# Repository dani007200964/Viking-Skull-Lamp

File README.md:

# Viking Skull Lamp 

## Introduction

I ​made this project for my brother. He loves Halloween and asked me to create a Viking-style lamp that has a glowing skull.
This is what comes out of this idea. I roughly had five months to test the device before publishing it. I can happily say
that in this period nothing went wrong with it. It just worked like a charm. Also, I have worked a lot on the documentation,
meanwhile. Here you can see what can this thing do.

## Features:
* 30 addressable LED to make it shine :rotating_light:
* Microphone for :studio_microphone:
  * Music reactive lighting :musical_note:
  * @ref clap_pattern "Clap switch" :clap:
* Foldable controls
* Interactive menu with a graphical display :joystick:
* Saving and loading the configuration parameters :floppy_disk:
* Light modes:
  * Rainbow :rainbow:
  * Candle :candle:
  * Pulse :loud_sound:
  * Komodo 3000 :sunny:
  * Color :art:
* Humidifier for spooky smoke effect :ghost:
* Magic runes on the front. They are glow-in-the-dark :star:

## Documentation

The full documentation with detailed assembly instructions can be found [here](https://dani007200964.github.io/Viking-Skull-Lamp/html/index.html).

## Donation

If you like my work, and if it was useful for you, please consider buying me a coffee or tipping. :coffee: :coffee: :coffee:

<a href='https://ko-fi.com/danielhajnal' target='_blank'>

## Contributing

Pull requests are welcome. For major changes, please open an issue first to discuss what you would like to change.

## Used Resources:

* [FastLED](https://github.com/FastLED/FastLED)
* [PlatformIO](https://platformio.org/)
* [Visual Studio Code](https://code.visualstudio.com/)
* [Atom](https://atom.io/)
* [Doxygen](https://doxygen.nl/manual/tables.html)
* [Doxygen Awesome Theme](https://github.com/jothepro/doxygen-awesome-css)
* [Graphviz](https://graphviz.org/)
* [FreeCAD](https://www.freecadweb.org/)
* [Blender](https://www.blender.org/)
* [Prusa Slicer](https://github.com/prusa3d/PrusaSlicer/releases)
* [Gimp](https://www.gimp.org/)
* [KiCad](https://www.kicad.org/)
* [Interactive HTML BOM](https://github.com/openscopeproject/InteractiveHtmlBom)
* [Inkscape](https://inkscape.org/)
* [OpenShot](https://www.openshot.org/)
* [model-viewer](https://modelviewer.dev/)

## License & Copyright

© Daniel Hajnal

:email: hajnal.daniel96@gmail.com

Software is licensed under the __MIT__ License, and the hardware and the mechanical parts are licensed under the __Creative Commons__ [BY-NC-SA](https://creativecommons.org/licenses/by-nc-sa/4.0/) license.

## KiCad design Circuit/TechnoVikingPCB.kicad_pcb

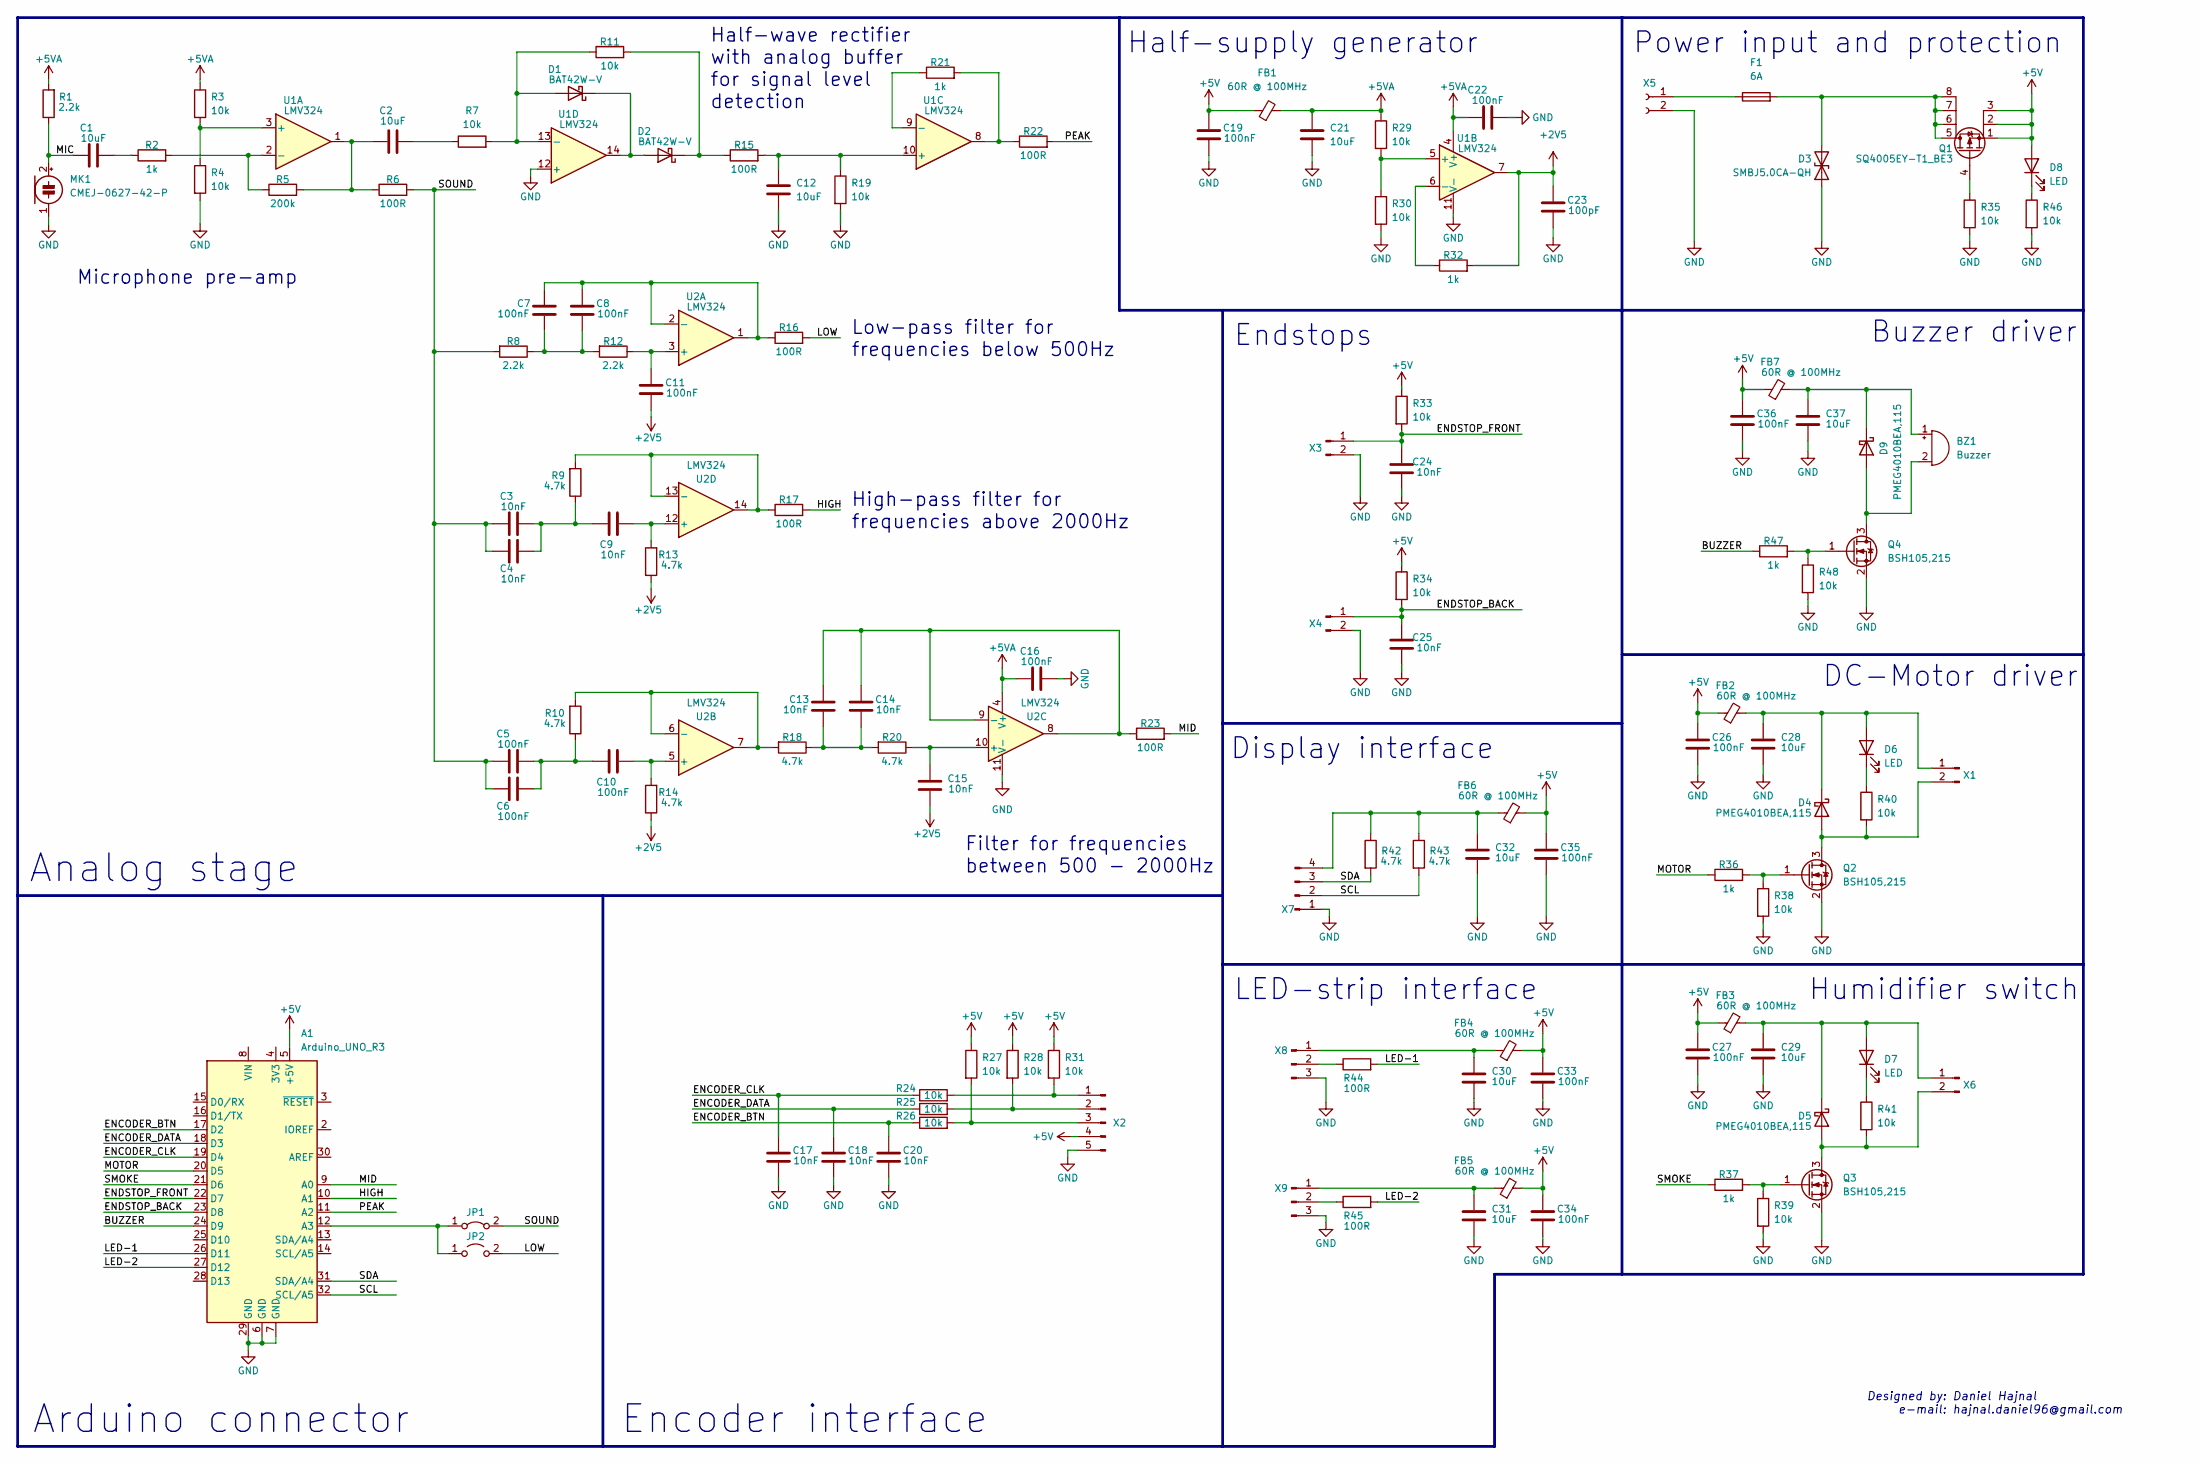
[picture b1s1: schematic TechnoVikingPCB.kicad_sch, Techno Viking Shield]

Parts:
A1: Arduino_UNO_R3; Arduino_R3_Extended; MPN 61304011121
BZ1: Buzzer; MagneticBuzzer_PUI_AT-0927-TT-6-R; MPN AT-0927-TT-6-R
C1, C2, C12, C21, C28, C29, C30, C31, C32, C37: 10uF; R_0805_2012Metric_Pad1.20x1.40mm_HandSolder; MPN GRM21BR61C106KE15K
C3, C4, C9, C13, C14, C15, C17, C18, C20, C24, C25: 10nF; R_0603_1608Metric_Pad0.98x0.95mm_HandSolder; MPN CC0603KRX7R7BB103
C5, C6, C7, C8, C10, C11, C16, C19, C22, C26, C27, C33, C34, C35, C36: 100nF; R_0603_1608Metric_Pad0.98x0.95mm_HandSolder; MPN CC0603JRX7R7BB104
C23: 100pF; R_0603_1608Metric_Pad0.98x0.95mm_HandSolder; MPN CC0603KRX7R7BB101
D1, D2: BAT42W-V; D_SOD-123; MPN BAT42W-G3-08
D3: SMBJ5.0CA-QH; D_SMB_Handsoldering; MPN SMBJ5.0CA-QH
D4, D5, D9: PMEG4010BEA,115; D_SOD-323_HandSoldering; MPN PMEG4010BEA,115
D6, D7: LED; LED_0603_1608Metric_Pad1.05x0.95mm_HandSolder; MPN APT1608SYC/J3-AMT
D8: LED; LED_0603_1608Metric_Pad1.05x0.95mm_HandSolder; MPN APT1608ZGC-AMT
F1: 6A; Fuse_1206_3216Metric_Pad1.42x1.75mm_HandSolder; MPN 0685P6000-01
FB1, FB2, FB3, FB4, FB5, FB6, FB7: 60R @ 100MHz; L_0603_1608Metric_Pad1.05x0.95mm_HandSolder; MPN BLM18PG600SZ1D
JP1: Jumper_2_Bridged; SolderJumper-2_P1.3mm_Bridged_Pad1.0x1.5mm
JP2: Jumper_2_Open; SolderJumper-2_P1.3mm_Open_Pad1.0x1.5mm
MK1: CMEJ-0627-42-P; Mic 6mm; MPN CMEJ-0627-42-P
Q1: SQ4005EY-T1_BE3; SO-8_3.9x4.9mm_P1.27mm; MPN SQ4005EY-T1_BE3
Q2, Q3, Q4: BSH105,215; SOT-23; MPN BSH105,215
R1, R8, R12: 2.2k; R_0603_1608Metric_Pad0.98x0.95mm_HandSolder; MPN CRCW06032K20FKEAC
R2, R21, R32, R36, R37, R47: 1k; R_0603_1608Metric_Pad0.98x0.95mm_HandSolder; MPN CRCW06031K00JNEC
R3, R4, R7, R11, R19, R24, R25, R26, R27, R28, R29, R30, R31, R33, R34, R35, R38, R39, R40, R41, R46, R48: 10k; R_0603_1608Metric_Pad0.98x0.95mm_HandSolder; MPN RCG060310K0FKEA
R5: 200k; R_0603_1608Metric_Pad0.98x0.95mm_HandSolder; MPN CRCW0603200KFKEAC
R6, R15, R16, R17, R22, R23, R44, R45: 100R; R_0603_1608Metric_Pad0.98x0.95mm_HandSolder; MPN CRCW0603100RJNEAC
R9, R10, R13, R14, R18, R20, R42, R43: 4.7k; R_0603_1608Metric_Pad0.98x0.95mm_HandSolder; MPN CRCW06034K70JNEC
U1, U2: LMV324; SOIC-14_3.9x8.7mm_P1.27mm; MPN LMV324IDR
X1, X3, X4, X6: Conn_01x02_Male; JST_PH_S2B-PH-K_1x02_P2.00mm_Horizontal; MPN S2B-PH-K-S (LF)(SN)
X2: Conn_01x05_Male; JST_PH_S5B-PH-K_1x05_P2.00mm_Horizontal; MPN S5B-PH-K-S (LF)(SN)
X5: Conn_01x02_Female; TerminalBlock_4Ucon_1x02_P3.50mm_Horizontal; MPN 39357-0002
X7: Conn_01x04_Male; JST_PH_S4B-PH-K_1x04_P2.00mm_Horizontal; MPN S4B-PH-K-S (LF)(SN)
X8, X9: Conn_01x03_Male; JST_PH_B3B-PH-K_1x03_P2.00mm_Vertical; MPN B3B-PH-K-S(LF)(SN)

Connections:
+2V5: C11.1, C15.1, C23.1, R13.1, R14.1, R32.2, U1.7
+5V: A1.5 (+5V), C19.2, C26.2, C27.2, C33.2, C34.2, C35.2, C36.2, D8.2 (A), FB1.1, FB2.1, FB3.1, FB4.2, FB5.2, FB6.2, FB7.1, Q1.1 (S), Q1.2 (S), Q1.3 (S), R27.1, R28.1, R31.1, R33.1, R34.1, X2.4
+5VA: C16.1, C21.2, C22.1, FB1.2, R1.2, R3.1, R29.1, U1.4 (V+), U2.4 (V+)
/BUZZER: A1.24 (D9), R47.1
/ENCODER_BTN: A1.17 (D2), C20.1, R26.1
/ENCODER_CLK: A1.19 (D4), C17.1, R24.1
/ENCODER_DATA: A1.18 (D3), C18.1, R25.1
/ENDSTOP_BACK: A1.23 (D8), C25.1, R34.2, X4.1
/ENDSTOP_FRONT: A1.22 (D7), C24.1, R33.2, X3.1
/HIGH: A1.10 (A1), R17.2
/LED-1: A1.26 (D11), R44.2
/LED-2: A1.27 (D12), R45.2
/LOW: JP2.2 (B), R16.2
/MIC: C1.1, MK1.2 (+), R1.1
/MID: A1.9 (A0), R23.2
/MOTOR: A1.20 (D5), R36.1
/PEAK: A1.11 (A2), R22.2
/SCL: A1.32 (SCL/A5), R43.2, X7.2
/SDA: A1.31 (SDA/A4), R42.2, X7.3
/SMOKE: A1.21 (D6), R37.1
/SOUND: C3.2, C4.2, C5.2, C6.2, JP1.2 (B), R6.2, R8.2
GND: A1.6 (GND), A1.7 (GND), A1.29 (GND), C12.1, C16.2, C17.2, C18.2, C19.1, C20.2, C21.1, C22.2, C23.2, C24.2, C25.2, C26.1, C27.1, C28.1, C29.1, C30.1, C31.1, C32.1, C33.1, C34.1, C35.1, C36.1, C37.1, D3.1 (A1), MK1.1 (-), Q2.2 (S), Q3.2 (S), Q4.2 (S), R4.2, R19.2, R30.2, R35.2, R38.2, R39.2, R46.2, R48.2, U1.11 (V-), U1.12 (+), U2.11 (V-), X2.5, X3.2, X4.2, X5.2, X7.1, X8.3, X9.3
unnamed: A1.12 (A3), JP1.1 (A), JP2.1 (A)
unnamed: BZ1.1 (-), C37.2, D9.1 (K), FB7.2
unnamed: BZ1.2 (+), D9.2 (A), Q4.3 (D)
unnamed: C1.2, R2.1
unnamed: C2.1, R5.2, R6.1, U1.1
unnamed: C2.2, R7.1
unnamed: C3.1, C4.1, C9.2, R9.1
unnamed: C7.1, C8.1, R8.1, R12.2
unnamed: C7.2, C8.2, R16.1, U2.1, U2.2 (-)
unnamed: C9.1, R13.2, U2.12 (+)
unnamed: C10.1, R14.2, U2.5 (+)
unnamed: C5.1, C6.1, C10.2, R10.1
unnamed: C11.2, R12.1, U2.3 (+)
unnamed: C12.2, R15.2, R19.1, U1.10 (+)
unnamed: C13.1, C14.1, R18.1, R20.2
unnamed: C13.2, C14.2, R23.1, U2.8, U2.9 (-)
unnamed: C15.2, R20.1, U2.10 (+)
unnamed: C28.2, D4.1 (K), D6.2 (A), FB2.2, X1.1
unnamed: C29.2, D5.1 (K), D7.2 (A), FB3.2, X6.1
unnamed: C30.2, FB4.1, X8.1
unnamed: C31.2, FB5.1, X9.1
unnamed: C32.2, FB6.1, R42.1, R43.1, X7.4
unnamed: D1.1 (K), D2.2 (A), U1.14
unnamed: D1.2 (A), R7.2, R11.1, U1.13 (-)
unnamed: D2.1 (K), R11.2, R15.1
unnamed: D3.2 (A2), F1.2, Q1.5 (D), Q1.6 (D), Q1.7 (D), Q1.8 (D)
unnamed: D4.2 (A), Q2.3 (D), R40.2, X1.2
unnamed: D5.2 (A), Q3.3 (D), R41.2, X6.2
unnamed: D6.1 (K), R40.1
unnamed: D7.1 (K), R41.1
unnamed: D8.1 (K), R46.1
unnamed: F1.1, X5.1
unnamed: Q1.4 (G), R35.1
unnamed: Q2.1 (G), R36.2, R38.1
unnamed: Q3.1 (G), R37.2, R39.1
unnamed: Q4.1 (G), R47.2, R48.1
unnamed: R2.2, R5.1, U1.2 (-)
unnamed: R3.2, R4.1, U1.3 (+)
unnamed: R10.2, R18.2, U2.6 (-), U2.7
unnamed: R9.2, R17.1, U2.13 (-), U2.14
unnamed: R21.1, U1.9 (-)
unnamed: R21.2, R22.1, U1.8
unnamed: R24.2, R31.2, X2.1
unnamed: R25.2, R28.2, X2.2
unnamed: R26.2, R27.2, X2.3
unnamed: R29.2, R30.1, U1.5 (+)
unnamed: R32.1, U1.6 (-)
unnamed: R44.1, X8.2
unnamed: R45.1, X9.2

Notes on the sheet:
High-pass filter for frequencies above 2000Hz
Half-supply generator
Arduino connector
Encoder interface
Filter for frequencies between 500 - 2000Hz
Endstops
LED-strip interface
Low-pass filter for frequencies below 500Hz
Display interface
Power input and protection
Buzzer driver
Designed by: Daniel Hajnal e-mail: hajnal.daniel96@gmail.com
Analog stage
Humidifier switch
Half-wave rectifier with analog buffer for signal level detection
DC-Motor driver
Microphone pre-amp

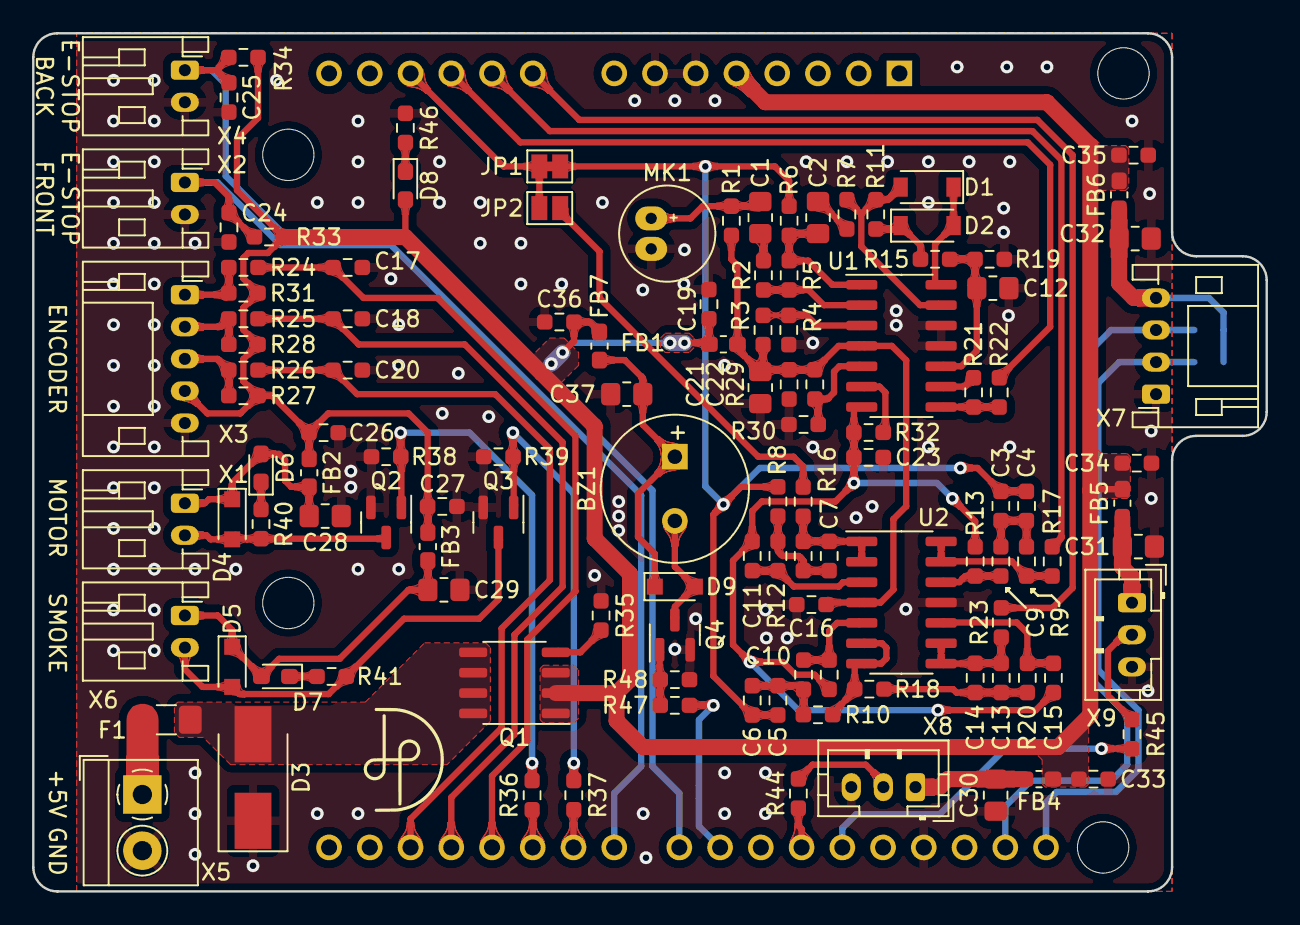
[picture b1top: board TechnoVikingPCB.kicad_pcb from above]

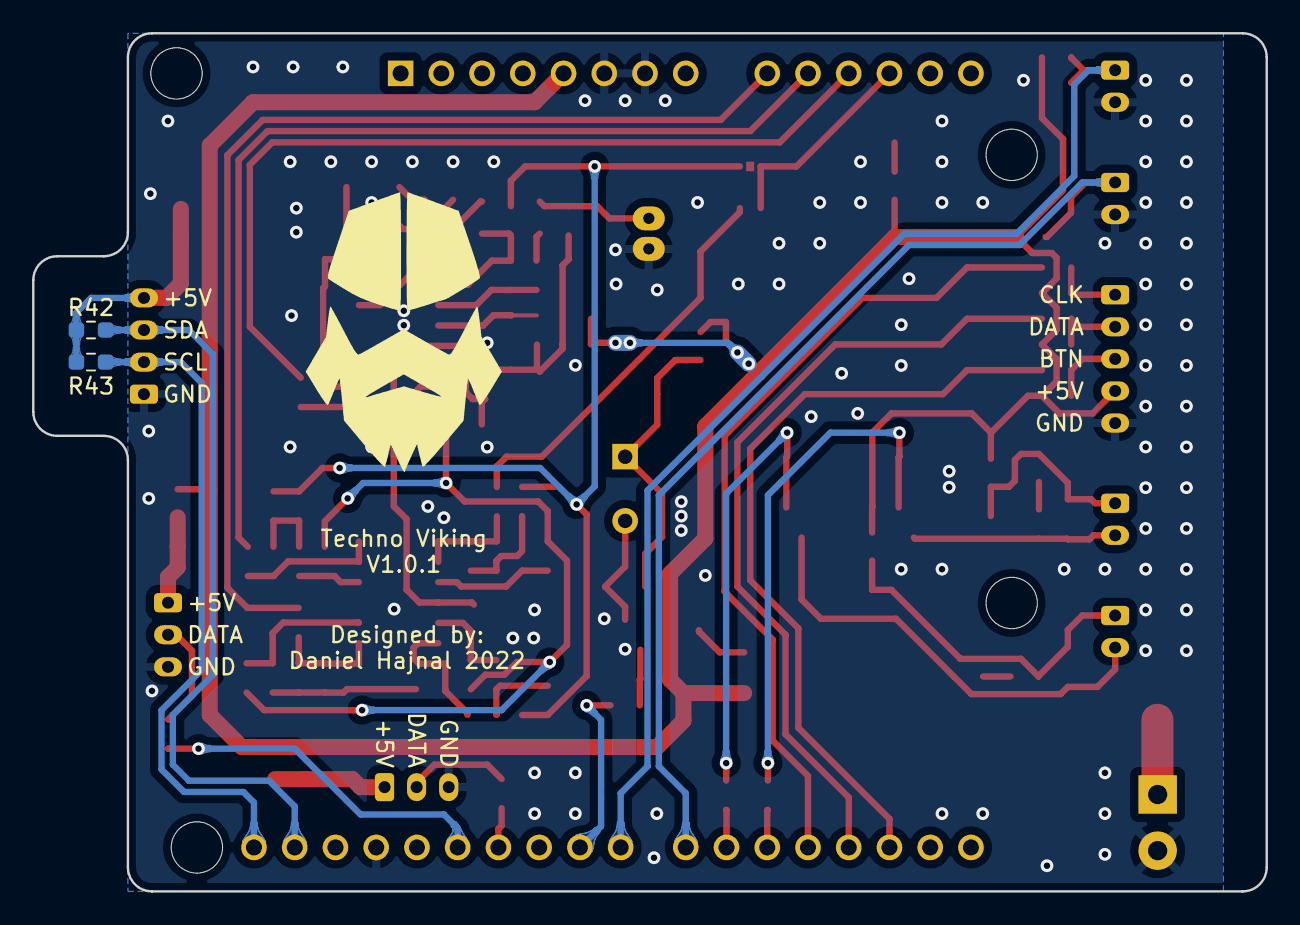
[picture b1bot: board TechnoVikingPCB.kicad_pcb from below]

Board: 2 copper layers, 76.9 x 53.5 mm, 122 parts (3 on the bottom side), 71 nets.

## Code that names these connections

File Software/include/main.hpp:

/*
 * Created on May 28 2022
 *
 * Copyright (c) 2022 - Daniel Hajnal
 * hajnal.daniel96@gmail.com
 * This file is part of the Viking Skull Lamp project.
 * Modified 2022.06.27
*/

/*
MIT License
Copyright (c) 2022 Daniel Hajnal
Permission is hereby granted, free of charge, to any person obtaining a copy
of this software and associated documentation files (the "Software"), to deal
in the Software without restriction, including without limitation the rights
to use, copy, modify, merge, publish, distribute, sublicense, and/or sell
copies of the Software, and to permit persons to whom the Software is
furnished to do so, subject to the following conditions:
The above copyright notice and this permission notice shall be included in all
copies or substantial portions of the Software.
THE SOFTWARE IS PROVIDED "AS IS", WITHOUT WARRANTY OF ANY KIND, EXPRESS OR
IMPLIED, INCLUDING BUT NOT LIMITED TO THE WARRANTIES OF MERCHANTABILITY,
FITNESS FOR A PARTICULAR PURPOSE AND NONINFRINGEMENT. IN NO EVENT SHALL THE
AUTHORS OR COPYRIGHT HOLDERS BE LIABLE FOR ANY CLAIM, DAMAGES OR OTHER
LIABILITY, WHETHER IN AN ACTION OF CONTRACT, TORT OR OTHERWISE, ARISING FROM,
OUT OF OR IN CONNECTION WITH THE SOFTWARE OR THE USE OR OTHER DEALINGS IN THE
SOFTWARE.
*/

#ifndef MAIN_HPP__
#define MAIN_HPP__

#include "Arduino.h"
#include "globalResources.hpp"
#include "oled.hpp"
#include "menu.hpp"
#include "motorControl.hpp"
#include "lightControl.hpp"
#include "buzzerControl.hpp"
#include "configuration.hpp"
#include "fogMachine.hpp"
#include <avr/wdt.h>

/// The encoder button is connected to pin 2 on the Arduino.
#define ENCODER_BTN 2

/// The encoder data line is connected to pin 4 on the Arduino.
#define ENCODER_DATA 4

/// The encoder clock line is connected to pin 3 on the Arduino.
#define ENCODER_CLK 3

// The buzzer is connected to pin 9 on the Arduino.
#define BUZZER 9
/*
    ____       ____            ____     ______            _____      
   / __ \___  / __/___ ___  __/ / /_   / ____/___  ____  / __(_)___ _
  / / / / _ \/ /_/ __ `/ / / / / __/  / /   / __ \/ __ \/ /_/ / __ `/
 / /_/ /  __/ __/ /_/ / /_/ / / /_   / /___/ /_/ / / / / __/ / /_/ / 
/_____/\___/_/  \__,_/\__,_/_/\__/   \____/\____/_/ /_/_/ /_/\__, /  
                                                            /____/   

*/
//---- This section contains the default configuration for the first boot up ----//

/// Default value for the light mode.
#define DEFAULT_LIGHT_MODE          LIGHT_MODE_RAINBOW

/// Default value for the user selected color.
#define DEFAULT_SELECTED_COLOR      0

/// Default value for the brightness.
#define DEFAULT_LIGHT_BRIGHTNESS    30

/// By default the buzzer is enabled.
#define DEFAULT_BUZZER_STATE        true

/// By default the clap switch is enabled.
#define DEFAULT_CLAP_SWITCH_STATE   true

/// By default the fog machine is enabled.
#define DEFAULT_FOG_STATE           true

/// Interrupt service for the encoder rotation events.
void encoderISR();

/// This function handles the button press detection.
void encoderButtonUpdate();

#endif

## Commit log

2022-09-01 Software components init.
2022-09-02 Documentation
    * Updated Style
    * Footer image
    * Graphs
2022-09-12 Documentation
    Step 9, 10, 11, 12
2022-09-21 Documented until Step 25.
    * Doxygen footer.html
2022-09-22 Documentation until step 52.
2022-09-22 Assembly steps are finished.
2022-09-23 Documentation.
2022-09-24 Documentation
    * Print Guide
2022-09-24 Source code documentation.
2022-09-24 Source code documentation
    fogMachine section.
2022-09-25 Required tools.
2022-09-25 Source documentation.
    * lightControl
2022-09-25 Source Documentation
    * main
2022-09-25 Source documentation
    * menu
2022-09-25 Source Documentation
    * motorControl
2022-09-26 Documentation
    * Issue templates
    * BOM
2022-09-26 Issue template emoji.
2022-09-26 Issue descriptions.
2022-09-26 Documentation
    Grammar check.
2022-09-27 Documentation.
    Skull support fix.
2022-09-27 Video with iframe
2022-09-27 VIdeo fix.
2022-09-27 Added cover images.
2022-10-07 Firmware documentation finished.
2022-10-14 Documentation fixes.
2022-10-14 Doc fix.
2022-10-14 Prusa Mini Gcodes
2022-10-16 Documentation
2022-10-16 Doc Fix
2022-10-16 Dic Fix
2023-10-20 MPN Fields are added to interactive BOM
